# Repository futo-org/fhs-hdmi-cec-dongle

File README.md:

# FHS CEC Dongle

The source repository for the FHS CEC Dongle. It gives Linux machines without CEC hardware an HDMI-CEC adapter: plug it in and the `fhs-cec` driver exposes it as `/dev/cecN` through the kernel's CEC framework.

| Path | What |
|---|---|
| `firmware/` | STM32F072 firmware |
| `driver/` | Linux kernel driver, DKMS package |
| `hardware/` | PCB and case |

## Releases

[release-please](https://github.com/googleapis/release-please) runs three release trains from conventional commits on `master`, each with its own release PR and tag:

| Train | Path | Tag | Assets |
|---|---|---|---|
| hardware | `hardware/` | `hardware-vX.Y.Z` | PCB and panel production files, STEP, case, programming package |
| firmware | `firmware/` | `firmware-vX.Y.Z` | `fhs-cec-firmware.hex`, `fhs-cec-firmware.bin` |
| driver | `driver/` | `driver-vX.Y.Z` | `fhs-cec-<version>.tar.gz` DKMS tarball |

Each release starts as a draft and is published once its assets are attached. If an asset job fails, run the release-please workflow by hand with the draft's tag to rebuild, attach and publish it. Delete any asset the failed run already attached first: uploads never replace an existing asset.

The workflow opens release PRs with `GITHUB_TOKEN`, so **Allow GitHub Actions to create and approve pull requests** must be on under Settings → Actions → General.

## License

- Everything not listed below: [Source First License 1.1](LICENSE)
- `driver/`: [GPL-2.0](driver/LICENSE), except `fhs-cec-proto.h` (GPL-2.0 OR MIT, shared with the firmware)
- Third-party code (`firmware/Drivers/`, `firmware/ref/`): its own license

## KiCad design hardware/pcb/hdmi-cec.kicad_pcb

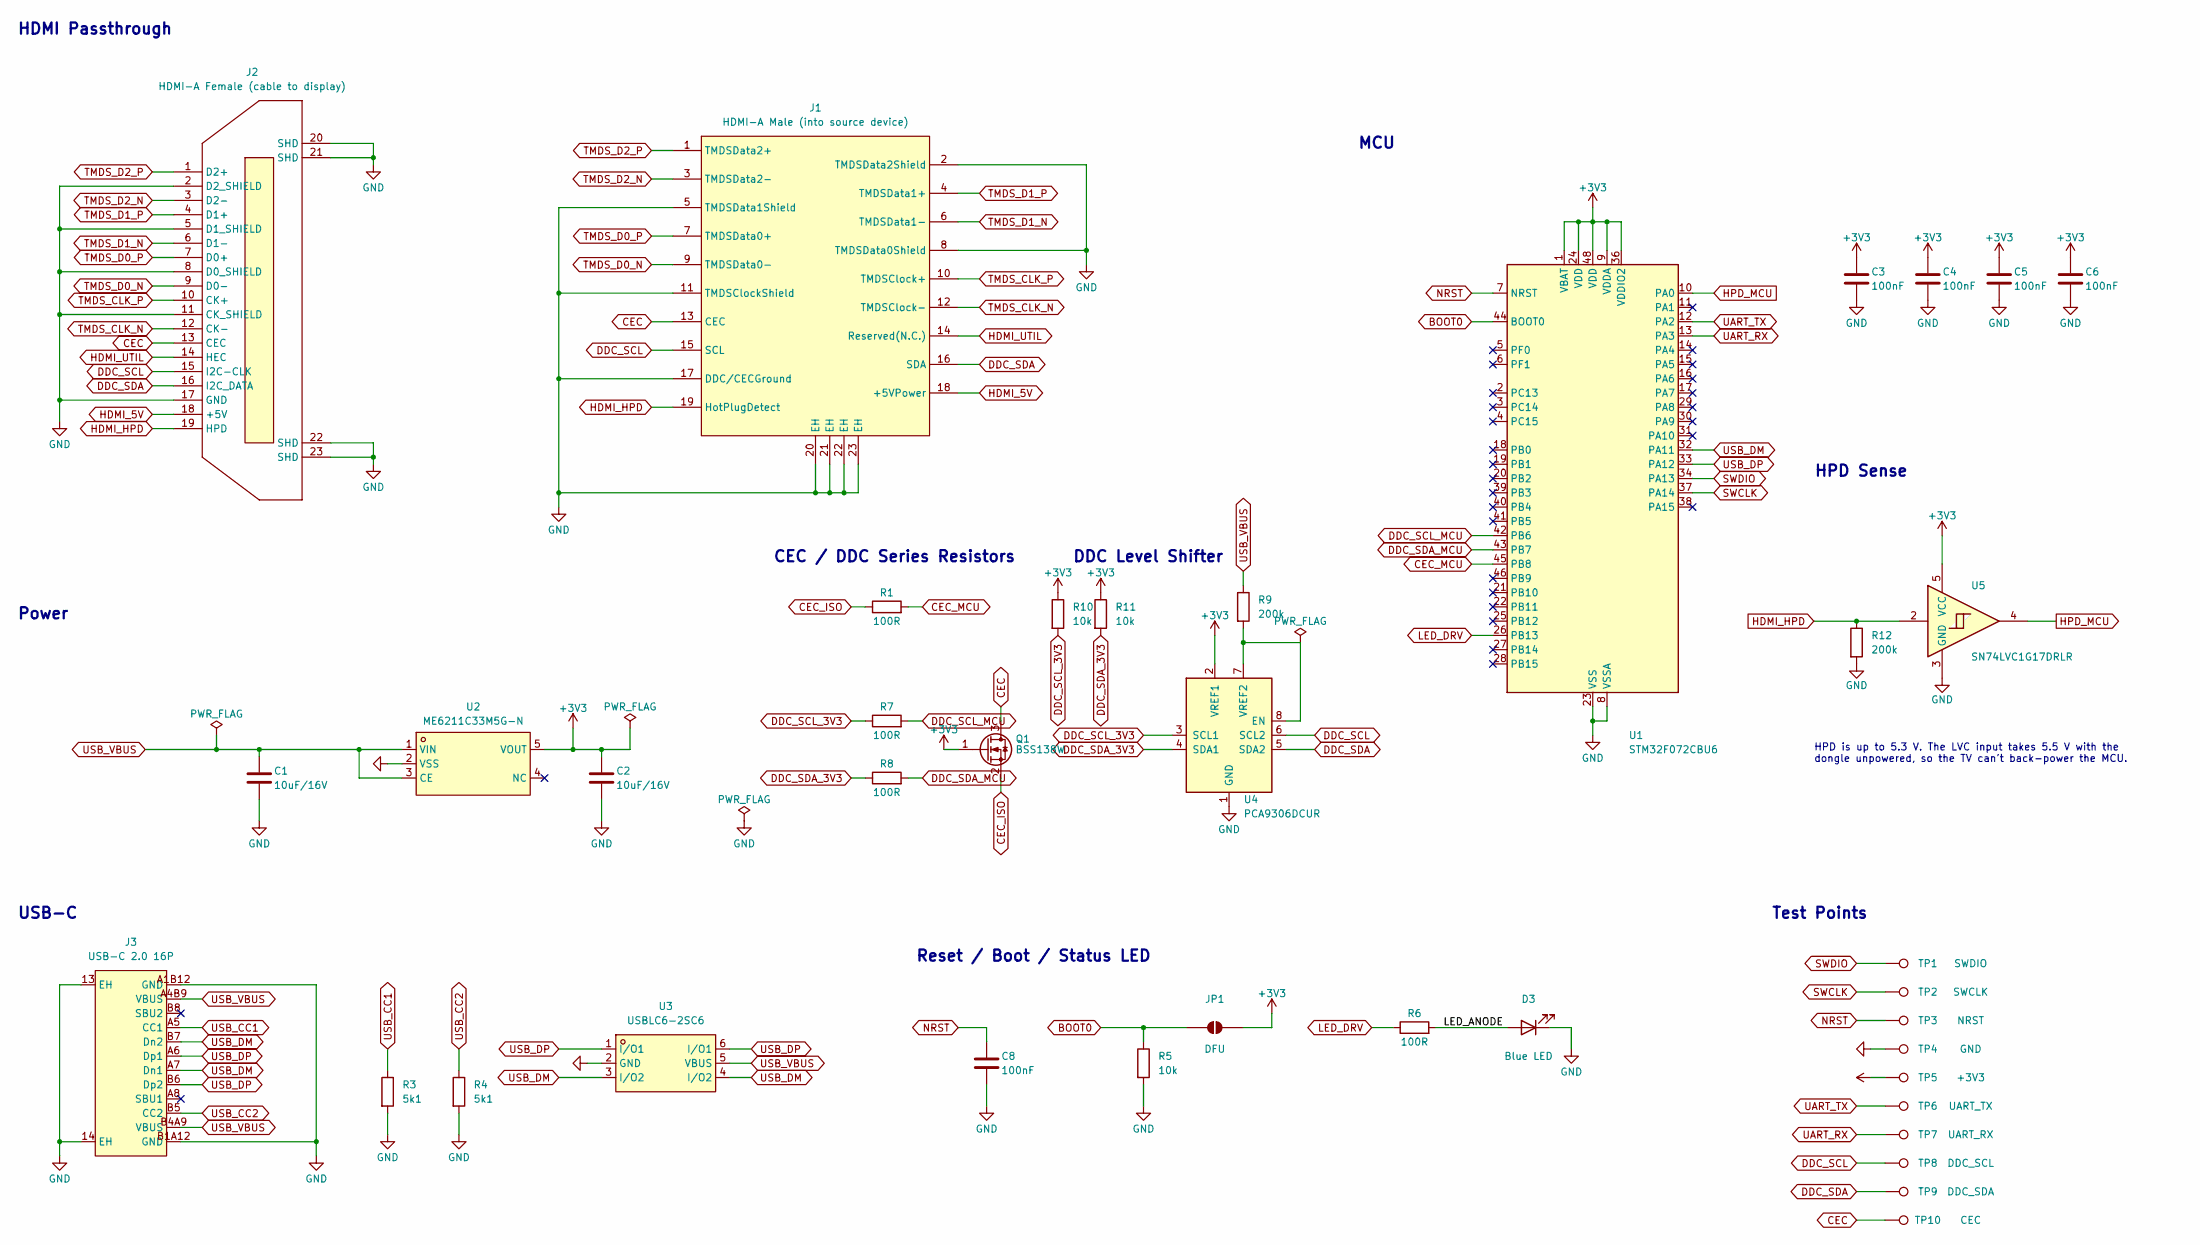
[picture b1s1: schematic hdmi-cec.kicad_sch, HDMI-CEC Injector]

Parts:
C1, C2: 10uF/16V; C0805; LCSC C15850
C3, C4, C5, C6, C8: 100nF; C0402; LCSC C1525
D3: Blue LED; LED0402-R-RD; LCSC C130724
J1: HDMI-A Male (into source device); HDMI-SMD_HYC109-HDMIA19-160; LCSC C711355
J2: HDMI-A Female (cable to display); HDMI-SMD_HDMI-19PIN-043; LCSC C2858275
J3: USB-C 2.0 16P; USB-C-SMD_TYPE-C-16PIN-2MD-073; LCSC C2765186
JP1: DFU; SolderJumper-2_P1.3mm_Open_Pad1.0x1.5mm
Q1: BSS138W; SOT-323_SC-70; LCSC C504052
R1: 100R; R_0402_1005Metric; LCSC C25076
R3, R4: 5k1; R0402; LCSC C25905
R5, R10, R11: 10k; R0402; LCSC C25744
R6, R7, R8: 100R; R0402; LCSC C25076
R9, R12: 200k; R0402; LCSC C25764
TP1: SWDIO; TestPoint_Pad_D0.8mm
TP2: SWCLK; TestPoint_Pad_D0.8mm
TP3: NRST; TestPoint_Pad_D0.8mm
TP4: GND; TestPoint_Pad_D0.8mm
TP5: +3V3; TestPoint_Pad_D0.8mm
TP6: UART_TX; TestPoint_Pad_D0.8mm
TP7: UART_RX; TestPoint_Pad_D0.8mm
TP8: DDC_SCL; TestPoint_Pad_D0.8mm
TP9: DDC_SDA; TestPoint_Pad_D0.8mm
TP10: CEC; TestPoint_Pad_D0.8mm
U1: STM32F072CBU6; UFQFPN-48_L7.0-W7.0-P0.50-BL-EP; LCSC C92504
U2: ME6211C33M5G-N; SOT-23-5_L3.0-W1.7-P0.95-LS2.8-BL; LCSC C82942
U3: USBLC6-2SC6; SOT-23-6_L2.9-W1.6-P0.95-LS2.8-BL; LCSC C2687116
U4: PCA9306DCUR; VSSOP-8_2.3x2mm_P0.5mm; LCSC C33196
U5: SN74LVC1G17DRLR; SOT-553; LCSC C2652096

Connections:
+3V3: C2.1, C3.1, C4.1, C5.1, C6.1, JP1.2 (B), Q1.1 (G), R10.1, R11.1, TP5.1 (1_1), U1.1 (VBAT), U1.9 (VDDA), U1.24 (VDD), U1.36 (VDDIO2), U1.48 (VDD), U2.5 (VOUT), U4.2 (VREF1), U5.5 (VCC)
/LED_ANODE: D3.2 (A), R6.2
BOOT0: JP1.1 (A), R5.1, U1.44 (BOOT0)
CEC: J1.13 (CEC), J2.13 (CEC), Q1.3 (D), TP10.1 (1_1)
CEC_ISO: Q1.2 (S), R1.1
CEC_MCU: R1.2, U1.45 (PB8)
DDC_SCL: J1.15 (SCL), J2.15 (I2C-CLK), TP8.1 (1_1), U4.6 (SCL2)
DDC_SCL_3V3: R7.1, R10.2, U4.3 (SCL1)
DDC_SCL_MCU: R7.2, U1.42 (PB6)
DDC_SDA: J1.16 (SDA), J2.16 (I2C_DATA), TP9.1 (1_1), U4.5 (SDA2)
DDC_SDA_3V3: R8.1, R11.2, U4.4 (SDA1)
DDC_SDA_MCU: R8.2, U1.43 (PB7)
GND: C1.2, C2.2, C3.2, C4.2, C5.2, C6.2, C8.2, D3.1 (K), J1.2 (TMDSData2Shield), J1.5 (TMDSData1Shield), J1.8 (TMDSData0Shield), J1.11 (TMDSClockShield), J1.17 (DDC/CECGround), J1.20 (EH), J1.21 (EH), J1.22 (EH), J1.23 (EH), J2.2 (D2_SHIELD), J2.5 (D1_SHIELD), J2.8 (D0_SHIELD), J2.11 (CK_SHIELD), J2.17 (GND), J2.20 (SHD), J2.21 (SHD), J2.22 (SHD), J2.23 (SHD), J3.13 (EH), J3.14 (EH), J3.A1B12 (GND), J3.B1A12 (GND), R3.2, R4.2, R5.2, R12.2, TP4.1 (1_1), U1.8 (VSSA), U1.23 (VSS), U1.35 (VSS), U1.47 (VSS), U1.49 (VSS), U2.2 (VSS), U3.2 (GND), U4.1 (GND), U5.3 (GND)
HDMI_5V: J1.18 (+5VPower), J2.18 (+5V)
HDMI_HPD: J1.19 (HotPlugDetect), J2.19 (HPD), R12.1, U5.2
HDMI_UTIL: J1.14 (Reserved(N.C.)), J2.14 (HEC)
HPD_MCU: U1.10 (PA0), U5.4
LED_DRV: R6.1, U1.26 (PB13)
NRST: C8.1, TP3.1 (1_1), U1.7 (NRST)
unnamed: R9.2, U4.7 (VREF2), U4.8 (EN)
SWCLK: TP2.1 (1_1), U1.37 (PA14)
SWDIO: TP1.1 (1_1), U1.34 (PA13)
TMDS_CLK_N: J1.12 (TMDSClock-), J2.12 (CK-)
TMDS_CLK_P: J1.10 (TMDSClock+), J2.10 (CK+)
TMDS_D0_N: J1.9 (TMDSData0-), J2.9 (D0-)
TMDS_D0_P: J1.7 (TMDSData0+), J2.7 (D0+)
TMDS_D1_N: J1.6 (TMDSData1-), J2.6 (D1-)
TMDS_D1_P: J1.4 (TMDSData1+), J2.4 (D1+)
TMDS_D2_N: J1.3 (TMDSData2-), J2.3 (D2-)
TMDS_D2_P: J1.1 (TMDSData2+), J2.1 (D2+)
UART_RX: TP7.1 (1_1), U1.13 (PA3)
UART_TX: TP6.1 (1_1), U1.12 (PA2)
USB_CC1: J3.A5 (CC1), R3.1
USB_CC2: J3.B5 (CC2), R4.1
USB_DM: J3.A7 (Dn1), J3.B7 (Dn2), U1.32 (PA11), U3.3 (I/O2), U3.4 (I/O2)
USB_DP: J3.A6 (Dp1), J3.B6 (Dp2), U1.33 (PA12), U3.1 (I/O1), U3.6 (I/O1)
USB_VBUS: C1.1, J3.A4B9 (VBUS), J3.B4A9 (VBUS), R9.1, U2.1 (VIN), U2.3 (CE), U3.5 (VBUS)

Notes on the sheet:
HDMI Passthrough
Power
USB-C
CEC / DDC Series Resistors
MCU
Reset / Boot / Status LED
Test Points
DDC Level Shifter
HPD Sense
HPD is up to 5.3 V. The LVC input takes 5.5 V with the dongle unpowered, so the TV can't back-power the MCU.

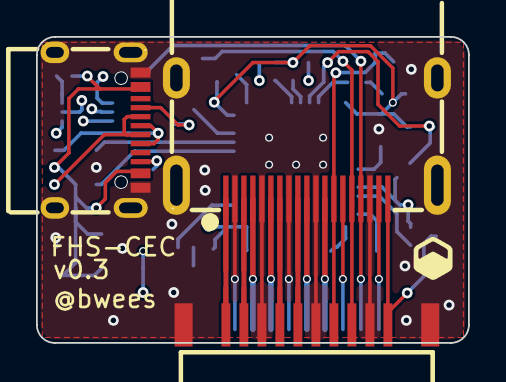
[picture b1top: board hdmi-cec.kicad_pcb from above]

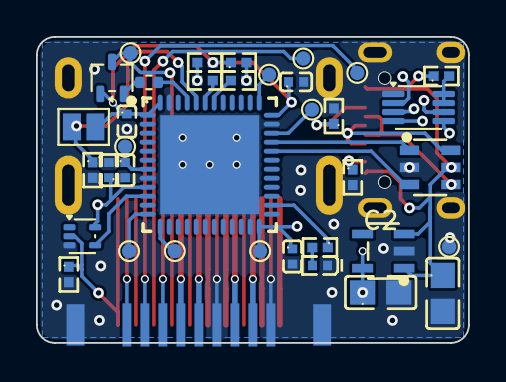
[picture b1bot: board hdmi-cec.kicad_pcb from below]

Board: 4 copper layers, 24.0 x 17.0 mm, 39 parts (36 on the bottom side), 37 nets.

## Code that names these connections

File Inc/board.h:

/* NUCLEO-F072RB pin map. Everything board-specific lives here. */
#ifndef BOARD_H
#define BOARD_H

#include "stm32f0xx_hal.h"

/* User LED LD2 */
#define BOARD_LED_PORT             GPIOA
#define BOARD_LED_PIN              GPIO_PIN_5
#define BOARD_LED_CLK_ENABLE()     __HAL_RCC_GPIOA_CLK_ENABLE()

/* USART2 -> ST-LINK virtual COM port (/dev/ttyACM0) */
#define BOARD_CONSOLE_UART          USART2
#define BOARD_CONSOLE_IRQn          USART2_IRQn
#define BOARD_CONSOLE_BAUD          115200U
#define BOARD_CONSOLE_PORT          GPIOA
#define BOARD_CONSOLE_PINS          (GPIO_PIN_2 | GPIO_PIN_3)  /* PA2 TX, PA3 RX */
#define BOARD_CONSOLE_AF            GPIO_AF1_USART2
#define BOARD_CONSOLE_CLK_ENABLE()  __HAL_RCC_USART2_CLK_ENABLE()
#define BOARD_CONSOLE_PORT_CLK_ENABLE() __HAL_RCC_GPIOA_CLK_ENABLE()

/* HDMI-CEC on PB8/AF0 (Arduino D15). HDMI pin 13, ground ref pin 17.
   Open drain, no internal pull: needs an external 27k to 3V3, the Nucleo has none. */
#define BOARD_CEC                   CEC
#define BOARD_CEC_PORT              GPIOB
#define BOARD_CEC_PIN               GPIO_PIN_8
#define BOARD_CEC_AF                GPIO_AF0_CEC
#define BOARD_CEC_IRQn              CEC_CAN_IRQn   /* NVIC 30, shared with CAN */
#define BOARD_CEC_IRQ_PRIORITY      3U             /* M0 has 0..3; below the console */
#define BOARD_CEC_CLK_ENABLE()      __HAL_RCC_CEC_CLK_ENABLE()
#define BOARD_CEC_PORT_CLK_ENABLE() __HAL_RCC_GPIOB_CLK_ENABLE()

#endif

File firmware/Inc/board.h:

/* FHS CEC dongle (hardware/pcb), STM32F072CBU6. Everything board-specific lives here. */
#ifndef BOARD_H
#define BOARD_H

#include "stm32f0xx_hal.h"

/* Status LED, active high */
#define BOARD_LED_PORT             GPIOB
#define BOARD_LED_PIN              GPIO_PIN_13
#define BOARD_LED_CLK_ENABLE()     __HAL_RCC_GPIOB_CLK_ENABLE()

/* USB FS on PA11/PA12, USB-C. No crystal: the USB clock is HSI48 trimmed by CRS
   against the host's start-of-frame. */
#define BOARD_USB_IRQn             USB_IRQn
#define BOARD_USB_IRQ_PRIORITY     2U

/* HDMI-CEC on PB8/AF0 through 100R and Q1, which cuts the pin off the bus when
   the dongle is unpowered. Q1 only passes a high when its source is pulled up,
   so the pin carries the internal pull-up. */
#define BOARD_CEC                   CEC
#define BOARD_CEC_PORT              GPIOB
#define BOARD_CEC_PIN               GPIO_PIN_8
#define BOARD_CEC_PULL              GPIO_PULLUP
#define BOARD_CEC_AF                GPIO_AF0_CEC
#define BOARD_CEC_IRQn              CEC_CAN_IRQn   /* NVIC 30, shared with CAN */
#define BOARD_CEC_IRQ_PRIORITY      3U             /* M0 has 0..3 */
#define BOARD_CEC_CLK_ENABLE()      __HAL_RCC_CEC_CLK_ENABLE()
#define BOARD_CEC_PORT_CLK_ENABLE() __HAL_RCC_GPIOB_CLK_ENABLE()

#define BOARD_DDC                  I2C1
#define BOARD_DDC_PORT              GPIOB
#define BOARD_DDC_SCL_PIN           GPIO_PIN_6
#define BOARD_DDC_SDA_PIN           GPIO_PIN_7
#define BOARD_DDC_AF                GPIO_AF1_I2C1
#define BOARD_DDC_CLK_ENABLE()      __HAL_RCC_I2C1_CLK_ENABLE()
#define BOARD_DDC_CLK_DISABLE()     __HAL_RCC_I2C1_CLK_DISABLE()
#define BOARD_DDC_PORT_CLK_ENABLE() __HAL_RCC_GPIOB_CLK_ENABLE()

#endif
